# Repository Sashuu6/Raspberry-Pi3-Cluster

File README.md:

# Raspberry-Pi3-Cluster
This repository contains everything about raspberry pi cluster using rack design.

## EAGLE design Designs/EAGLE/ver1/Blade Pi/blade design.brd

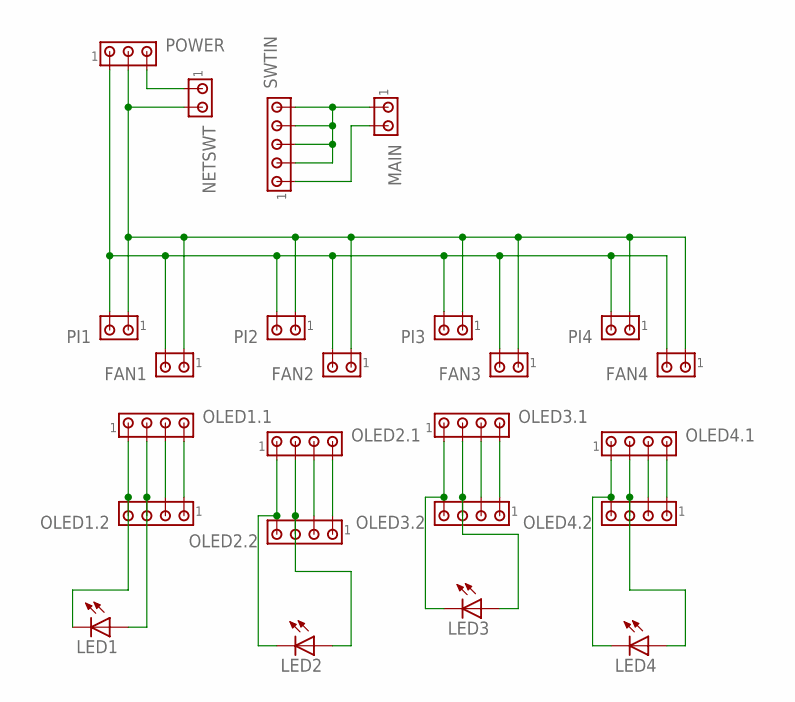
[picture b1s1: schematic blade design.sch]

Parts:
FAN1, FAN2, FAN3, FAN4: MTA02-156; 1X2MTA
LED1, LED2, LED3, LED4: LED_ELD260; LED_LD260
MAIN: MTA02-156; 1X2MTA
NETSWT: MTA02-156; 1X2MTA
OLED1.1, OLED1.2, OLED2.1, OLED2.2, OLED3.1, OLED3.2, OLED4.1, OLED4.2: MTA04-156; 1X4MTA
PI1, PI2, PI3, PI4: MTA02-156; 1X2MTA
POWER: MTA03-156; 1X3MTA
SWTIN: MTA05-156; 1X5MTA

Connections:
3.3V: MAIN.2, SWTIN.1
5V: FAN1.2, FAN2.2, FAN3.2, FAN4.2, PI1.2, PI2.2, PI3.2, PI4.2, POWER.1
12V: NETSWT.1, POWER.3
GND: FAN1.1, FAN2.1, FAN3.1, FAN4.1, NETSWT.2, PI1.1, PI2.1, PI3.1, PI4.1, POWER.2
GND1: LED1.K (C), OLED1.1.1, OLED1.2.4
GND2: LED2.K (C), OLED2.1.1, OLED2.2.4
GND3: LED3.K (C), OLED3.1.1, OLED3.2.4
GND4: LED4.K (C), OLED4.1.1, OLED4.2.4
SCL1: OLED1.1.3, OLED1.2.2
SCL2: OLED2.1.3, OLED2.2.2
SCL3: OLED3.1.3, OLED3.2.2
SCL4: OLED4.1.3, OLED4.2.2
SDA1: OLED1.1.4, OLED1.2.1
SDA2: OLED2.1.4, OLED2.2.1
SDA3: OLED3.1.4, OLED3.2.1
SDA4: OLED4.1.4, OLED4.2.1
SWTCH: MAIN.1, SWTIN.2, SWTIN.3, SWTIN.4, SWTIN.5
VCC1: LED1.A, OLED1.1.2, OLED1.2.3
VCC2: LED2.A, OLED2.1.2, OLED2.2.3
VCC3: LED3.A, OLED3.1.2, OLED3.2.3
VCC4: LED4.A, OLED4.1.2, OLED4.2.3

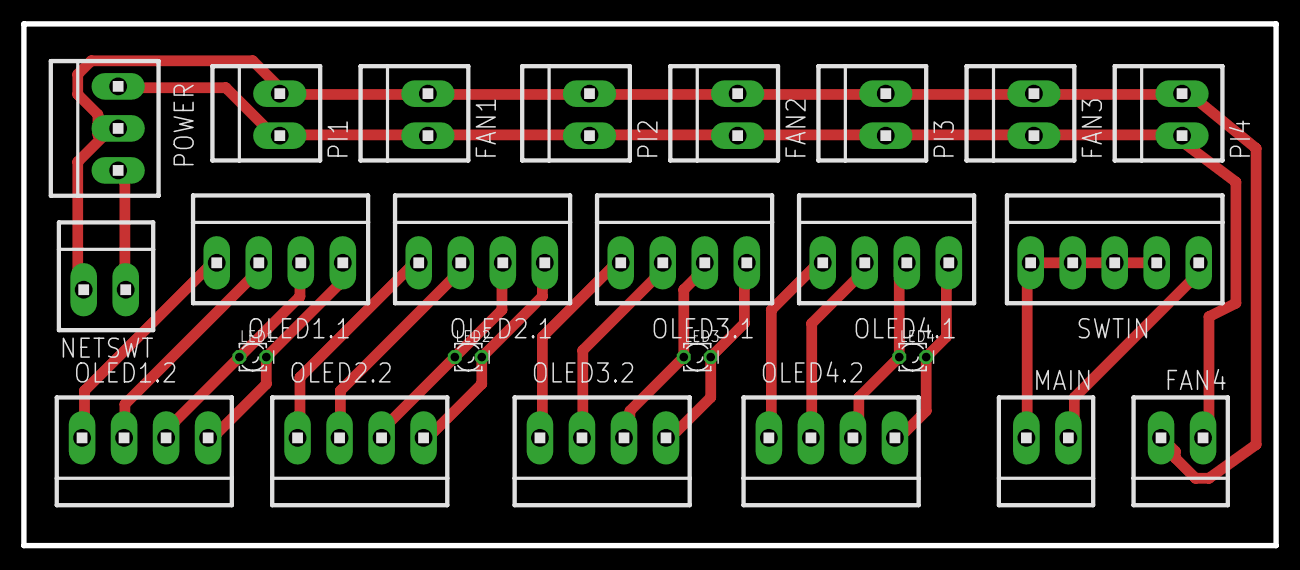
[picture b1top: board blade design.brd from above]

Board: 2 copper layers, 118.1 x 49.2 mm, 24 parts (0 on the bottom side), 21 nets.

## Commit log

2018-05-17 Component list
    This is the component list for the build. This is not final.
2018-05-17 Daily commit #2
2018-05-21 Initial desig commit
2018-05-23 board design complete
2018-05-24 First design complete
2018-05-26 change in component list
2018-05-26 cluster program code complete
2018-05-26 phase 1 coding, complete
2018-05-28 design commit
2018-06-06 design complete
2018-08-25 Small changes
